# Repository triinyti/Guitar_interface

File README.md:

# Guitar_interface
Custom designed guitar interface for 48kHz/24 bit audio transmission via UAC (USB Audio Class) and mic output.

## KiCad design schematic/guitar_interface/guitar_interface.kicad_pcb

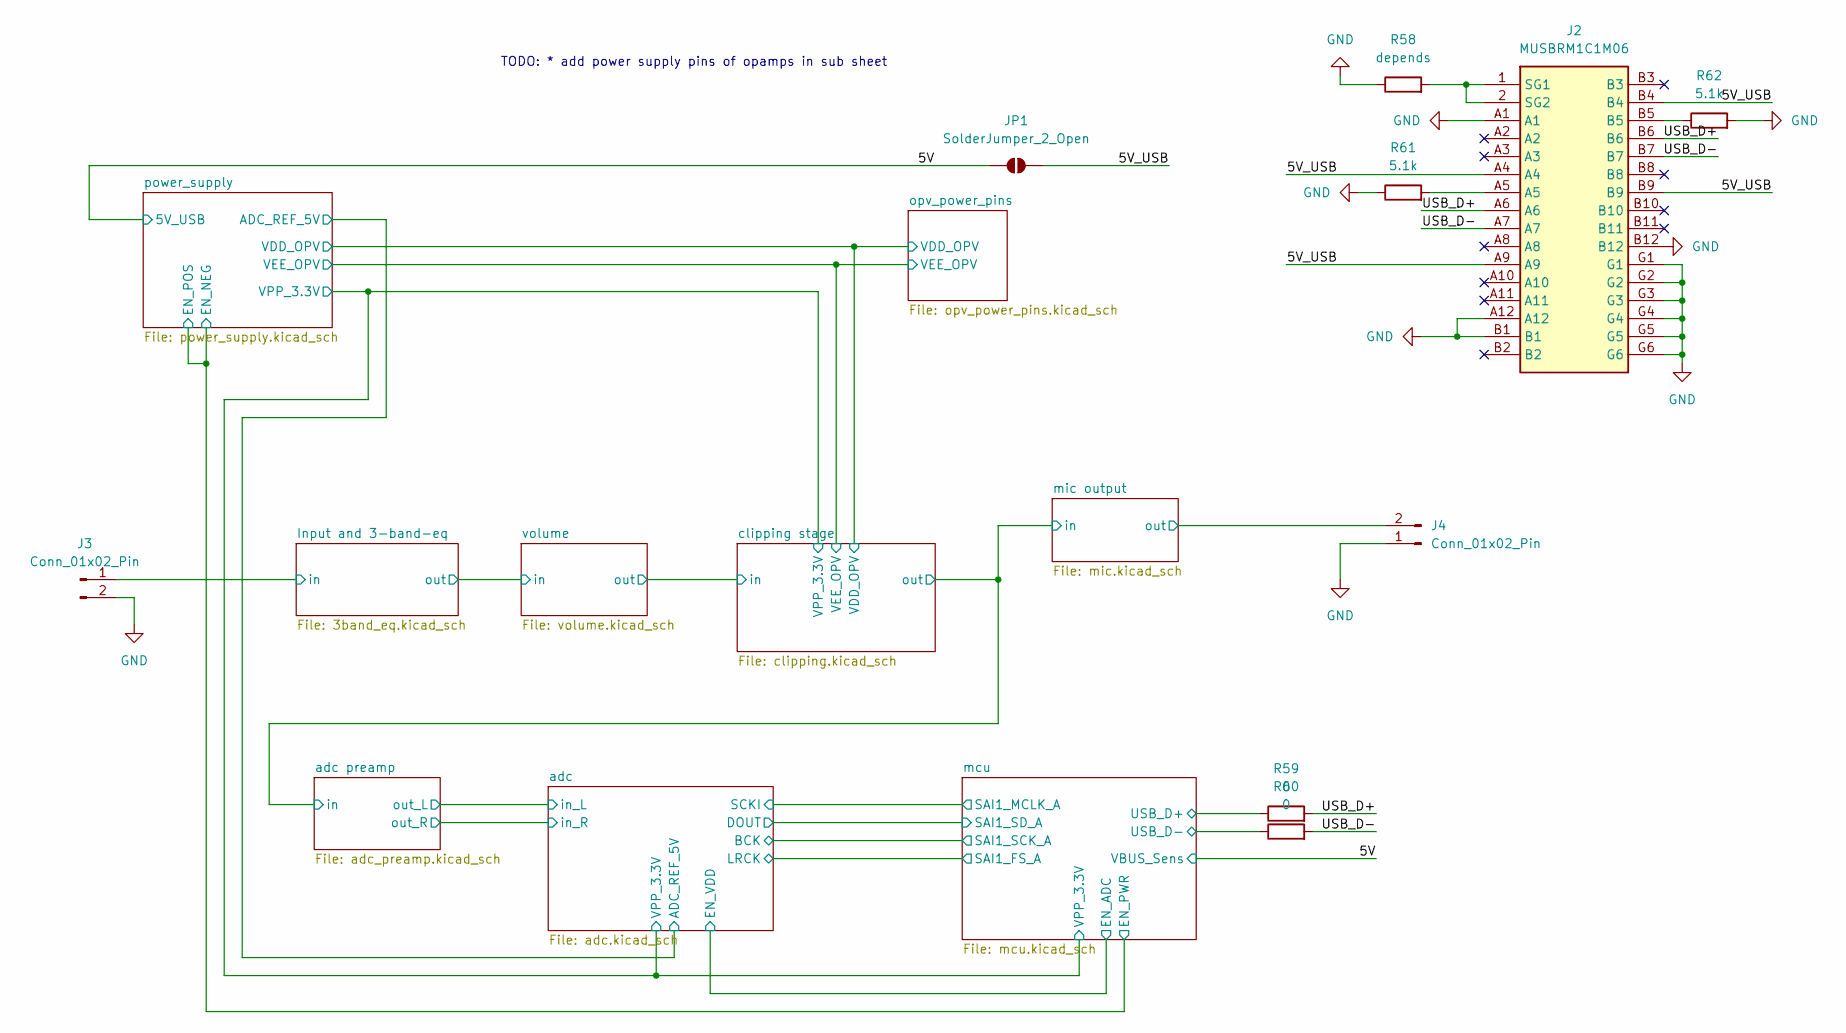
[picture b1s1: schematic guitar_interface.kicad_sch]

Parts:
J2: MUSBRM1C1M06; Mouser Part Number 523-MUSBRM1C1M06
J3, J4: Conn_01x02_Pin; PinSocket_1x02_P2.54mm_Vertical
JP1: SolderJumper_2_Open; SolderJumper-2_P1.3mm_Open_RoundedPad1.0x1.5mm
R58: depends; R_0603_1608Metric_Pad0.98x0.95mm_HandSolder
R59, R60: 0; R_0603_1608Metric_Pad0.98x0.95mm_HandSolder
R61, R62: 5.1k; R_0603_1608Metric_Pad0.98x0.95mm_HandSolder

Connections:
/5V: JP1.1 (A); also elsewhere on the board
/5V_USB: J2.A4, J2.A9, J2.B4, J2.B9, JP1.2 (B)
/Input and 3-band-eq/in: J3.1; also elsewhere on the board
/USB_D+: J2.A6, J2.B6, R59.2
/USB_D-: J2.A7, J2.B7, R60.2
/mcu/USB_D+: R59.1; also elsewhere on the board
/mcu/USB_D-: R60.1; also elsewhere on the board
/mic output/out: J4.2; also elsewhere on the board
GND: J2.A1, J2.A12, J2.B1, J2.B12, J2.G1, J2.G2, J2.G3, J2.G4, J2.G5, J2.G6, J3.2, J4.1, R58.1, R61.1, R62.2; also elsewhere on the board
unnamed: J2.A5, R61.2
unnamed: J2.B5, R62.1
unnamed: J2.1 (SG1), J2.2 (SG2), R58.2

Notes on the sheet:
TODO: * add power supply pins of opamps in sub sheet

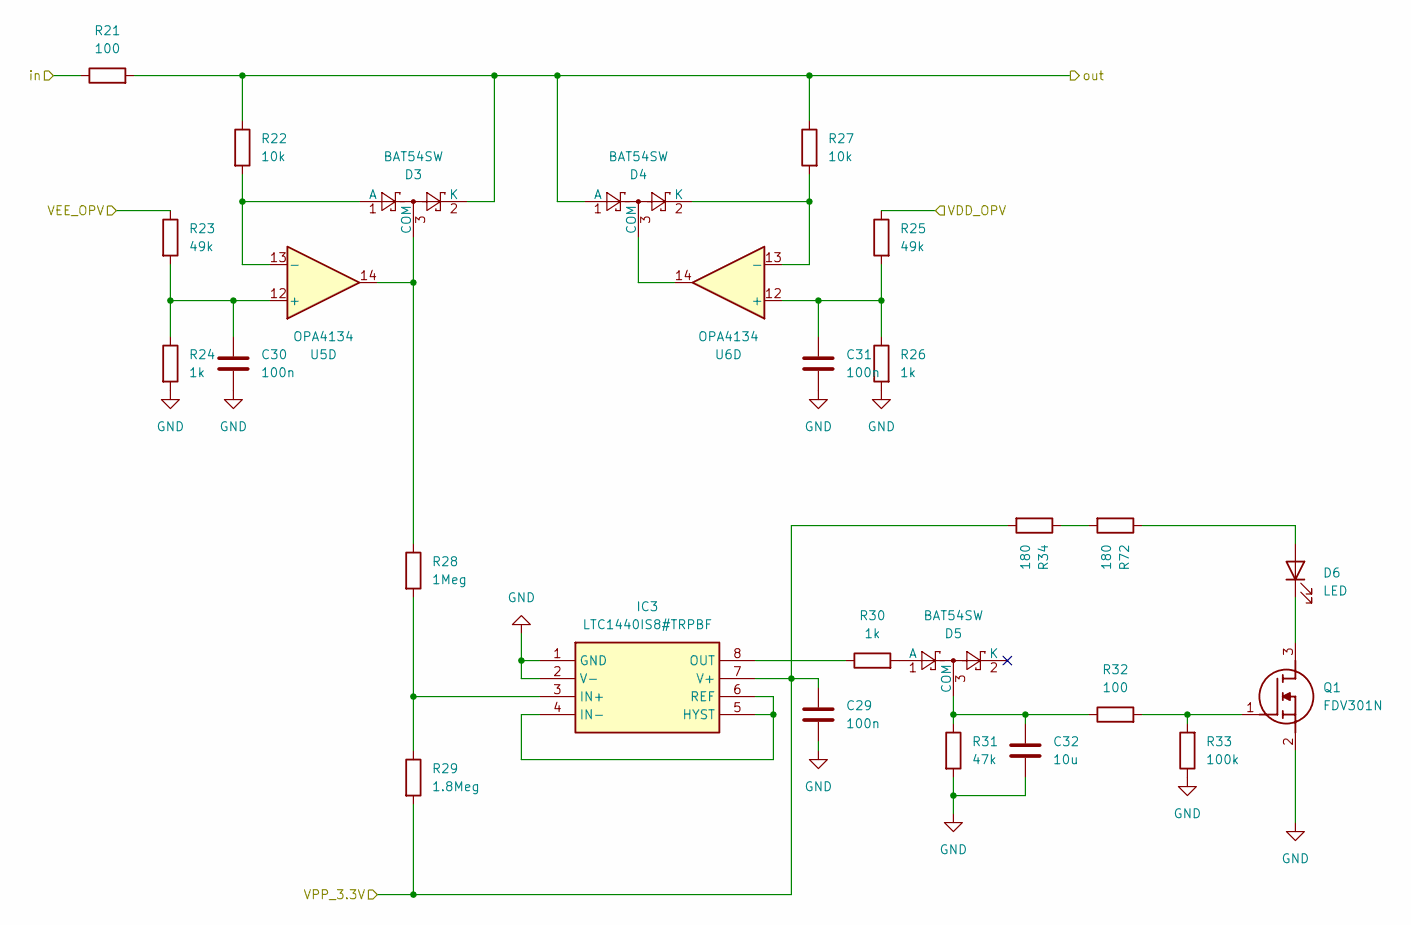
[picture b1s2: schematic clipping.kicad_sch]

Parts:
C29, C30, C31: 100n; C_0402_1005Metric_Pad0.74x0.62mm_HandSolder
C32: 10u; C_0603_1608Metric_Pad1.08x0.95mm_HandSolder
D3, D4, D5: BAT54SW; SOT-323_SC-70
D6: LED; LED_0603_1608Metric_Pad1.05x0.95mm_HandSolder
IC3: LTC1440IS8#TRPBF; SOIC127P599X175-8N; Mouser Part Number 584-LTC1440IS8#TRPBF
Q1: FDV301N; SOT96P237X111-3N; Mouser Part Number 512-FDV301N
R21, R32: 100; R_0603_1608Metric_Pad0.98x0.95mm_HandSolder
R22, R27: 10k; R_0603_1608Metric_Pad0.98x0.95mm_HandSolder
R23, R25: 49k; R_0603_1608Metric_Pad0.98x0.95mm_HandSolder
R24, R26, R30: 1k; R_0603_1608Metric_Pad0.98x0.95mm_HandSolder
R28: 1Meg; R_0603_1608Metric_Pad0.98x0.95mm_HandSolder
R29: 1.8Meg; R_0603_1608Metric_Pad0.98x0.95mm_HandSolder
R31: 47k; R_0603_1608Metric_Pad0.98x0.95mm_HandSolder
R33: 100k; R_0603_1608Metric_Pad0.98x0.95mm_HandSolder
R34, R72: 180; R_0603_1608Metric_Pad0.98x0.95mm_HandSolder
U5, U6: OPA4134; SOIC-14_3.9x8.7mm_P1.27mm

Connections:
/adc preamp/in: D3.2 (K), D4.1 (A), R21.2, R22.1, R27.1; also elsewhere on the board
/adc/VPP_3.3V: C29.1, IC3.7 (V+), R29.2, R34.2; also elsewhere on the board
/clipping stage/VDD_OPV: R25.1; also elsewhere on the board
/clipping stage/VEE_OPV: R23.1; also elsewhere on the board
/clipping stage/in: R21.1; also elsewhere on the board
GND: C29.2, C30.2, C31.2, C32.2, IC3.1 (GND), IC3.2 (V-), Q1.2 (S), R24.2, R26.2, R31.2, R33.1; also elsewhere on the board
unnamed: D3.1 (A), R22.2, U5.13 (-)
unnamed: D3.3 (COM), R28.1, U5.14
unnamed: D4.3 (COM), U6.14
unnamed: D4.2 (K), R27.2, U6.13 (-)
unnamed: D5.1 (A), R30.2
unnamed: C32.1, D5.3 (COM), R31.1, R32.1
unnamed: D6.2 (A), R72.1
unnamed: D6.1 (K), Q1.3 (D)
unnamed: IC3.4 (IN-), IC3.5 (HYST), IC3.6 (REF)
unnamed: IC3.3 (IN+), R28.2, R29.1
unnamed: IC3.8 (OUT), R30.1
unnamed: Q1.1 (G), R32.2, R33.2
unnamed: R34.1, R72.2
unnamed: C30.1, R23.2, R24.1, U5.12 (+)
unnamed: C31.1, R25.2, R26.1, U6.12 (+)

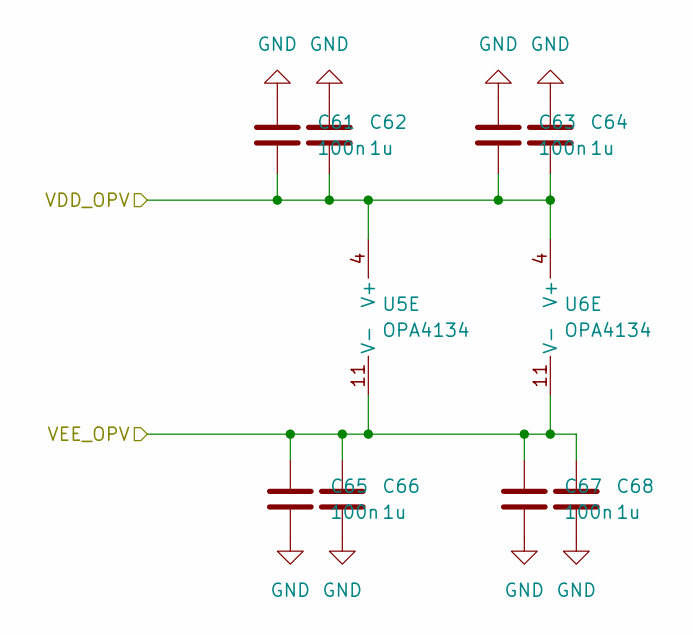
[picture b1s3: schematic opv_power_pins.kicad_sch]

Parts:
C61, C63, C65, C67: 100n; C_0402_1005Metric_Pad0.74x0.62mm_HandSolder
C62, C64, C66, C68: 1u; C_0603_1608Metric_Pad1.08x0.95mm_HandSolder
U5, U6: OPA4134; SOIC-14_3.9x8.7mm_P1.27mm

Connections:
/clipping stage/VDD_OPV: C61.2, C62.2, C63.2, C64.2, U5.4 (V+), U6.4 (V+); also elsewhere on the board
/clipping stage/VEE_OPV: C65.1, C66.1, C67.1, C68.1, U5.11 (V-), U6.11 (V-); also elsewhere on the board
GND: C61.1, C62.1, C63.1, C64.1, C65.2, C66.2, C67.2, C68.2; also elsewhere on the board

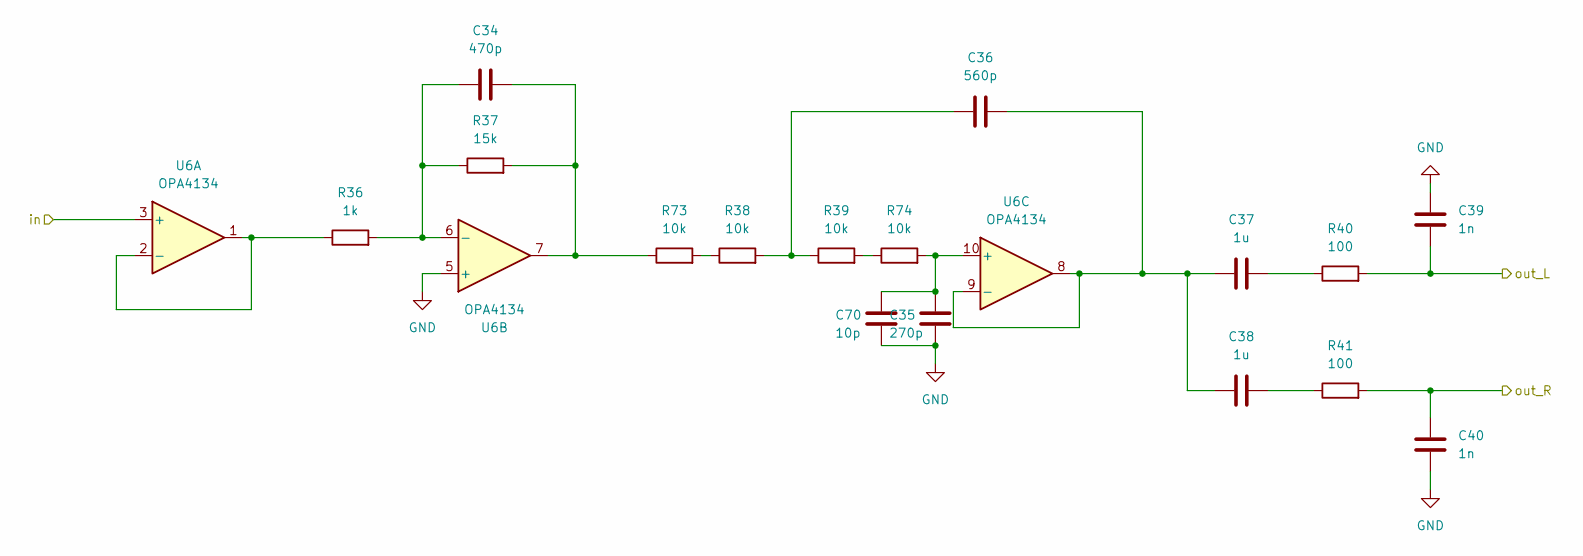
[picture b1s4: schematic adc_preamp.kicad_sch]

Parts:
C34: 470p; C_0603_1608Metric_Pad1.08x0.95mm_HandSolder
C35: 270p; C_0402_1005Metric_Pad0.74x0.62mm_HandSolder
C36: 560p; C_0805_2012Metric_Pad1.18x1.45mm_HandSolder
C37, C38: 1u; C_0603_1608Metric_Pad1.08x0.95mm_HandSolder
C39, C40: 1n; C_0402_1005Metric_Pad0.74x0.62mm_HandSolder
C70: 10p; C_0603_1608Metric_Pad1.08x0.95mm_HandSolder
R36: 1k; R_0603_1608Metric_Pad0.98x0.95mm_HandSolder
R37: 15k; R_0603_1608Metric_Pad0.98x0.95mm_HandSolder
R38, R39, R73, R74: 10k; R_0603_1608Metric_Pad0.98x0.95mm_HandSolder
R40, R41: 100; R_0603_1608Metric_Pad0.98x0.95mm_HandSolder
U6: OPA4134; SOIC-14_3.9x8.7mm_P1.27mm

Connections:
/adc preamp/in: U6.3 (+); also elsewhere on the board
/adc preamp/out_L: C39.1, R40.2; also elsewhere on the board
/adc preamp/out_R: C40.2, R41.2; also elsewhere on the board
GND: C35.2, C39.2, C40.1, C70.2, U6.5 (+); also elsewhere on the board
unnamed: C34.2, R37.2, R73.1, U6.7
unnamed: C36.1, R38.2, R39.1
unnamed: C37.2, R40.1
unnamed: C38.2, R41.1
unnamed: R38.1, R73.2
unnamed: R39.2, R74.1
unnamed: R36.1, U6.1, U6.2 (-)
unnamed: C34.1, R36.2, R37.1, U6.6 (-)
unnamed: C35.1, C70.1, R74.2, U6.10 (+)
unnamed: C36.2, C37.1, C38.1, U6.8, U6.9 (-)

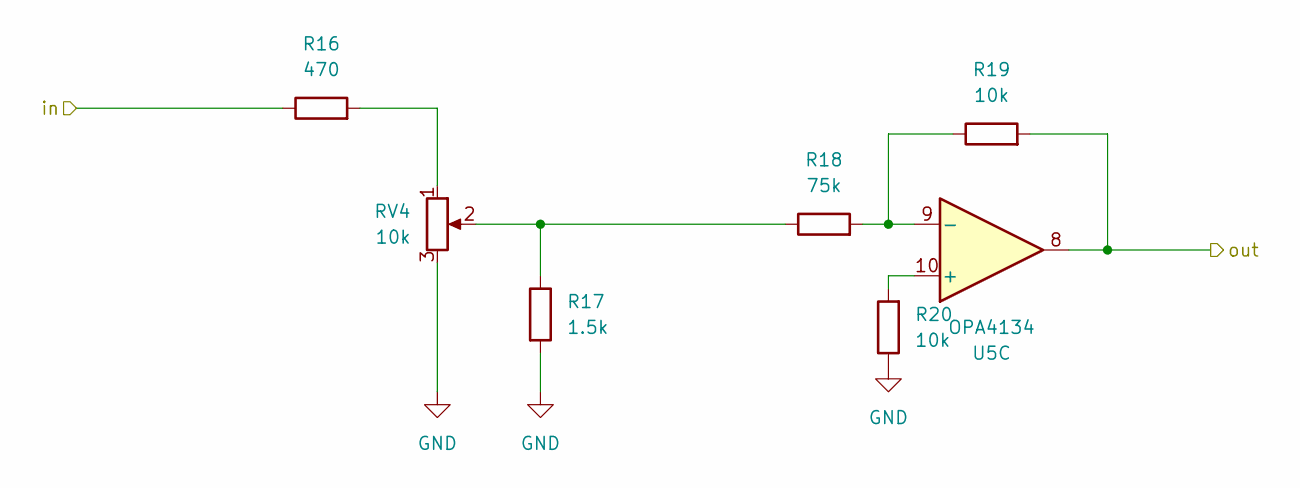
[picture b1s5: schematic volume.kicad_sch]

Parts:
R16: 470; R_0603_1608Metric_Pad0.98x0.95mm_HandSolder
R17: 1.5k; R_0603_1608Metric_Pad0.98x0.95mm_HandSolder
R18: 75k; R_0603_1608Metric_Pad0.98x0.95mm_HandSolder
R19, R20: 10k; R_0603_1608Metric_Pad0.98x0.95mm_HandSolder
RV4: 10k; PinHeader_1x03_P2.54mm_Vertical
U5: OPA4134; SOIC-14_3.9x8.7mm_P1.27mm

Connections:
/Input and 3-band-eq/out: R16.1; also elsewhere on the board
/clipping stage/in: R19.2, U5.8; also elsewhere on the board
GND: R17.2, R20.1, RV4.3; also elsewhere on the board
unnamed: R16.2, RV4.1
unnamed: R17.1, R18.1, RV4.2
unnamed: R20.2, U5.10 (+)
unnamed: R18.2, R19.1, U5.9 (-)

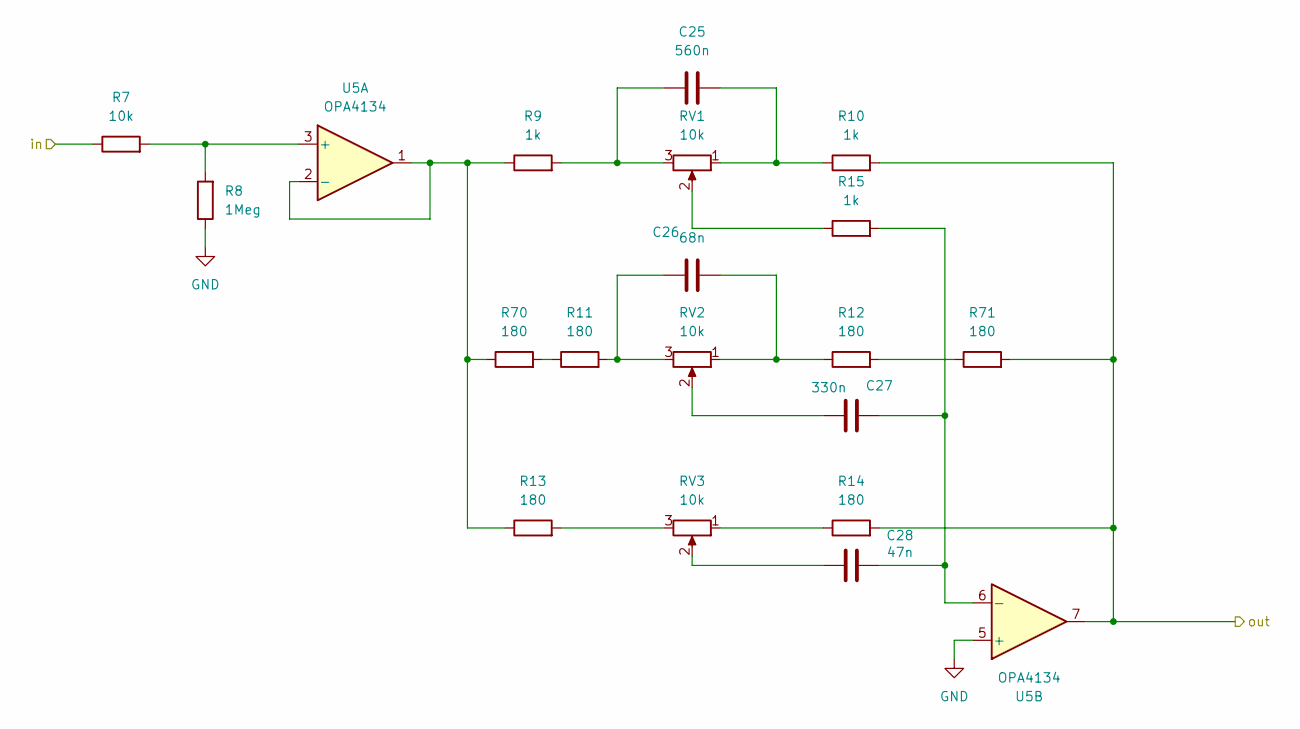
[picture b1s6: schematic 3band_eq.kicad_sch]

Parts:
C25: 560n; C_0805_2012Metric_Pad1.18x1.45mm_HandSolder
C26: 68n; C_0805_2012Metric_Pad1.18x1.45mm_HandSolder
C27: 330n; C_0805_2012Metric_Pad1.18x1.45mm_HandSolder
C28: 47n; C_0603_1608Metric_Pad1.08x0.95mm_HandSolder
R7: 10k; R_0603_1608Metric_Pad0.98x0.95mm_HandSolder
R8: 1Meg; R_0603_1608Metric_Pad0.98x0.95mm_HandSolder
R9, R10, R15: 1k; R_0603_1608Metric_Pad0.98x0.95mm_HandSolder
R11, R12, R13, R14, R70, R71: 180; R_0603_1608Metric_Pad0.98x0.95mm_HandSolder
RV1, RV2, RV3: 10k; PinHeader_1x03_P2.54mm_Vertical
U5: OPA4134; SOIC-14_3.9x8.7mm_P1.27mm

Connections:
/Input and 3-band-eq/in: R7.1; also elsewhere on the board
/Input and 3-band-eq/out: R10.2, R14.2, R71.2, U5.7; also elsewhere on the board
GND: R8.1, U5.5 (+); also elsewhere on the board
unnamed: C25.1, R9.2, RV1.3
unnamed: C25.2, R10.1, RV1.1
unnamed: C26.1, R11.2, RV2.3
unnamed: C26.2, R12.1, RV2.1
unnamed: C27.1, RV2.2
unnamed: C28.1, RV3.2
unnamed: R11.1, R70.2
unnamed: R12.2, R71.1
unnamed: R13.2, RV3.3
unnamed: R14.1, RV3.1
unnamed: R15.1, RV1.2
unnamed: R7.2, R8.2, U5.3 (+)
unnamed: R9.1, R13.1, R70.1, U5.1, U5.2 (-)
unnamed: C27.2, C28.2, R15.2, U5.6 (-)

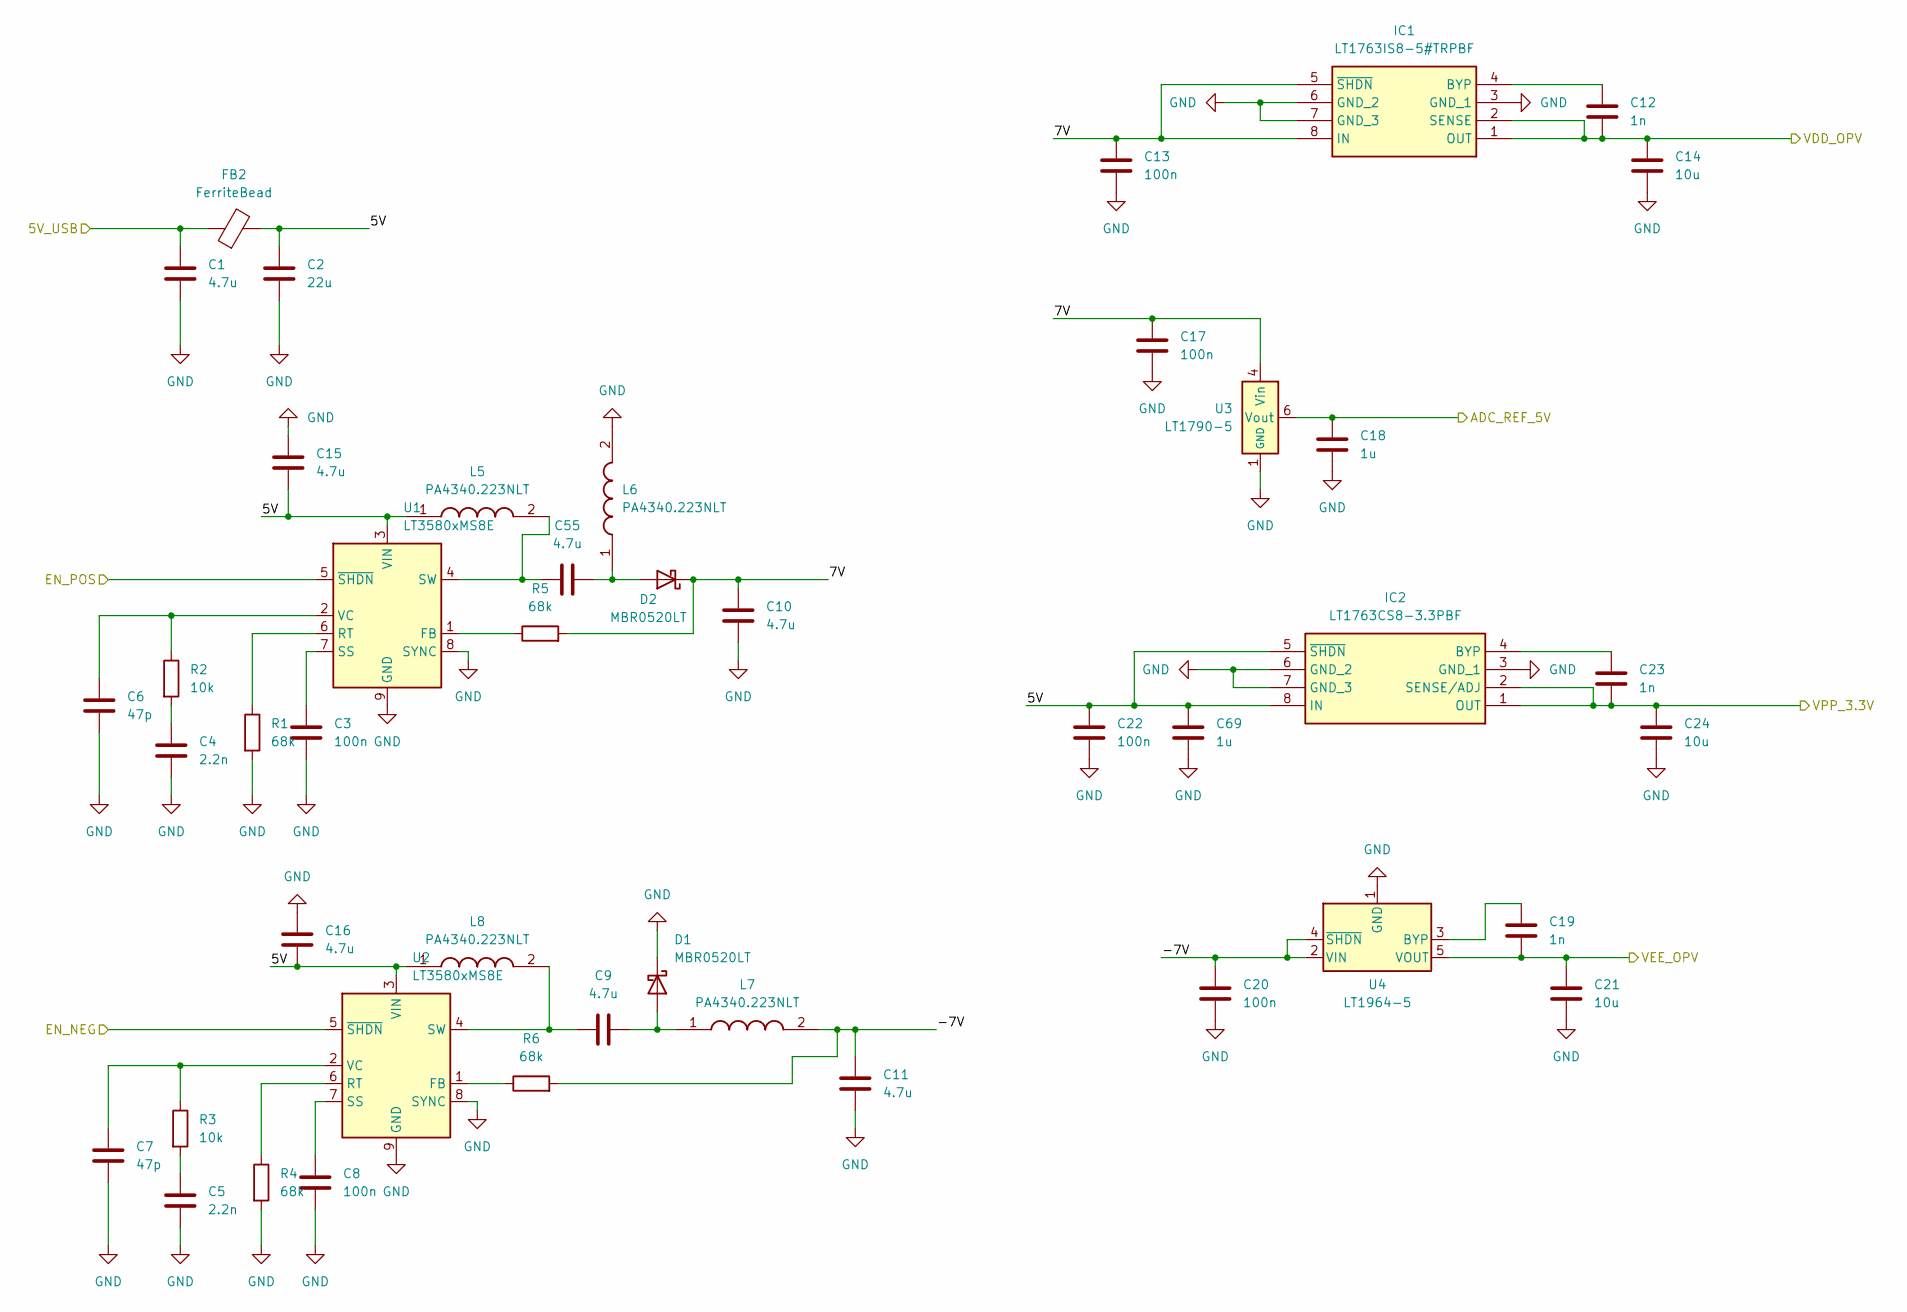
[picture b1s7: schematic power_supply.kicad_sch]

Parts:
C1, C9, C10, C11, C15, C16, C55: 4.7u; C_0805_2012Metric_Pad1.18x1.45mm_HandSolder
C2: 22u; C_0603_1608Metric_Pad1.08x0.95mm_HandSolder
C3, C8, C13, C17, C20, C22: 100n; C_0402_1005Metric_Pad0.74x0.62mm_HandSolder
C4, C5: 2.2n; C_0402_1005Metric_Pad0.74x0.62mm_HandSolder
C6, C7: 47p; C_0402_1005Metric_Pad0.74x0.62mm_HandSolder
C12, C19, C23: 1n; C_0402_1005Metric_Pad0.74x0.62mm_HandSolder
C14, C21, C24: 10u; C_0603_1608Metric_Pad1.08x0.95mm_HandSolder
C18, C69: 1u; C_0603_1608Metric_Pad1.08x0.95mm_HandSolder
D1, D2: MBR0520LT; D_SOD-123
FB2: FerriteBead; R_1206_3216Metric
IC1: LT1763IS8-5#TRPBF; SOIC127P599X175-8N; Mouser Part Number 584-LT1763IS8-5TRPBF
IC2: LT1763CS8-3.3PBF; SOIC127P599X175-8N; Manufacturer_Part_Number LT1763CS8-3.3PBF
L5, L6, L7, L8: PA4340.223NLT; INDPM6054X300N; Mouser Part Number 673-PA4340.223NLT
R1, R4, R5, R6: 68k; R_0603_1608Metric_Pad0.98x0.95mm_HandSolder
R2, R3: 10k; R_0603_1608Metric_Pad0.98x0.95mm_HandSolder
U1, U2: LT3580xMS8E; MSOP-8-1EP_3x3mm_P0.65mm_EP1.68x1.88mm
U3: LT1790-5; TSOT-23-6
U4: LT1964-5; TSOT-23-5

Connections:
/5V: C1.1, FB2.1; also elsewhere on the board
/adc/ADC_REF_5V: C18.1, U3.6 (Vout); also elsewhere on the board
/adc/VPP_3.3V: C23.2, C24.1, IC2.1 (OUT), IC2.2 (SENSE/ADJ); also elsewhere on the board
/clipping stage/VDD_OPV: C12.2, C14.1, IC1.1 (OUT), IC1.2 (SENSE); also elsewhere on the board
/clipping stage/VEE_OPV: C19.2, C21.1, U4.5 (VOUT); also elsewhere on the board
/mcu/EN_PWR: U1.5 (~SHDN), U2.5 (~SHDN); also elsewhere on the board
/power_supply/5V: C2.1, C15.1, C16.1, C22.1, C69.1, FB2.2, IC2.5 (~SHDN), IC2.8 (IN), L5.1, L8.1, U1.3 (VIN), U2.3 (VIN)
/power_supply/7V: C10.2, C13.1, C17.1, D2.1 (K), IC1.5 (~SHDN), IC1.8 (IN), R5.2, U3.4 (Vin)
/power_supply/-7V: C11.2, C20.1, L7.2, R6.2, U4.2 (VIN), U4.4 (~SHDN)
GND: C1.2, C2.2, C3.2, C4.2, C5.2, C6.2, C7.2, C8.2, C10.1, C11.1, C13.2, C14.2, C15.2, C16.2, C17.2, C18.2, C20.2, C21.2, C22.2, C24.2, C69.2, D1.1 (K), IC1.3 (GND_1), IC1.6 (GND_2), IC1.7 (GND_3), IC2.3 (GND_1), IC2.6 (GND_2), IC2.7 (GND_3), L6.2, R1.2, R4.2, U1.8 (SYNC), U1.9 (GND), U2.8 (SYNC), U2.9 (GND), U3.1 (GND), U3.2 (GND), U4.1 (GND); also elsewhere on the board
unnamed: C4.1, R2.2
unnamed: C5.1, R3.2
unnamed: C9.2, D1.2 (A), L7.1
unnamed: C55.1, D2.2 (A), L6.1
unnamed: C12.1, IC1.4 (BYP)
unnamed: C23.1, IC2.4 (BYP)
unnamed: R5.1, U1.1 (FB)
unnamed: R1.1, U1.6 (RT)
unnamed: C3.1, U1.7 (SS)
unnamed: C55.2, L5.2, U1.4 (SW)
unnamed: C6.1, R2.1, U1.2 (VC)
unnamed: R6.1, U2.1 (FB)
unnamed: R4.1, U2.6 (RT)
unnamed: C8.1, U2.7 (SS)
unnamed: C9.1, L8.2, U2.4 (SW)
unnamed: C7.1, R3.1, U2.2 (VC)
unnamed: C19.1, U4.3 (BYP)

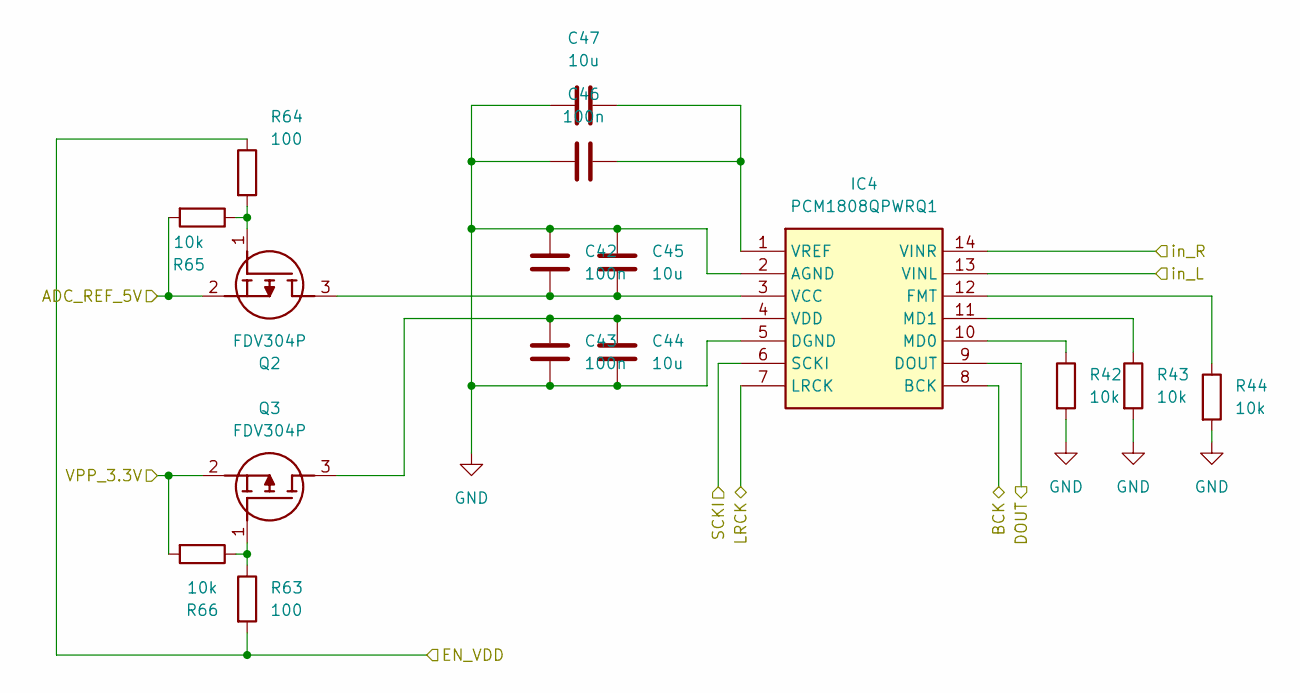
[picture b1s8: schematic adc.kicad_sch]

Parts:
C42, C43, C46: 100n; C_0402_1005Metric_Pad0.74x0.62mm_HandSolder
C44, C45, C47: 10u; C_0603_1608Metric_Pad1.08x0.95mm_HandSolder
IC4: PCM1808QPWRQ1; SOP65P640X120-14N; Mouser Part Number 595-PCM1808QPWRQ1
Q2, Q3: FDV304P; SOT95P251X112-3N; Mouser Part Number 512-FDV304P
R42, R43, R44, R65, R66: 10k; R_0603_1608Metric_Pad0.98x0.95mm_HandSolder
R63, R64: 100; R_0603_1608Metric_Pad0.98x0.95mm_HandSolder

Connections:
/adc preamp/out_L: IC4.13 (VINL); also elsewhere on the board
/adc preamp/out_R: IC4.14 (VINR); also elsewhere on the board
/adc/ADC_REF_5V: Q2.2 (S), R65.2; also elsewhere on the board
/adc/BCK: IC4.8 (BCK); also elsewhere on the board
/adc/DOUT: IC4.9 (DOUT); also elsewhere on the board
/adc/EN_VDD: R63.2, R64.1; also elsewhere on the board
/adc/LRCK: IC4.7 (LRCK); also elsewhere on the board
/adc/SCKI: IC4.6 (SCKI); also elsewhere on the board
/adc/VPP_3.3V: Q3.2 (S), R66.2; also elsewhere on the board
GND: C42.2, C43.1, C44.1, C45.2, C46.2, C47.2, IC4.2 (AGND), IC4.5 (DGND), R42.2, R43.2, R44.2; also elsewhere on the board
unnamed: IC4.12 (FMT), R44.1
unnamed: IC4.10 (MD0), R42.1
unnamed: IC4.11 (MD1), R43.1
unnamed: C42.1, C45.1, IC4.3 (VCC), Q2.3 (D)
unnamed: C43.2, C44.2, IC4.4 (VDD), Q3.3 (D)
unnamed: C46.1, C47.1, IC4.1 (VREF)
unnamed: Q2.1 (G), R64.2, R65.1
unnamed: Q3.1 (G), R63.1, R66.1

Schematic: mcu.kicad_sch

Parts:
C41, C48, C49, C50, C51, C52, C59, C60: 100n; C_0402_1005Metric_Pad0.74x0.62mm_HandSolder
C53, C56: 15p; C_0201_0603Metric_Pad0.64x0.40mm_HandSolder
C54: 4.7u; C_0805_2012Metric_Pad1.18x1.45mm_HandSolder
C57, C58: 2.2u; C_0603_1608Metric_Pad1.08x0.95mm_HandSolder
D7, D8: ESD321DPYR; DPY_R-PX1SON-N2_; Mouser Part Number 595-ESD321DPYR
D9: LED; LED_0603_1608Metric_Pad1.05x0.95mm_HandSolder
J1: Conn_ST_STDC14; FTSH-107-XX-YYY-D-K
R45, R47, R48, R49, R50, R53, R54, R55, R56, R57, R67: 470; R_0603_1608Metric_Pad0.98x0.95mm_HandSolder
R46, R51, R52: 10k; R_0603_1608Metric_Pad0.98x0.95mm_HandSolder
R68, R69: 0; R_0603_1608Metric_Pad0.98x0.95mm_HandSolder
U8: STM32F446VETx; LQFP-100_14x14mm_P0.5mm
Y1: LFXTAL032878; Manufacturer_Part_Number LFXTAL032878

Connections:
/5V: R51.2; also elsewhere on the board
/adc/BCK: R48.2; also elsewhere on the board
/adc/DOUT: R49.2; also elsewhere on the board
/adc/EN_VDD: R69.2; also elsewhere on the board
/adc/LRCK: R47.2; also elsewhere on the board
/adc/SCKI: R50.1; also elsewhere on the board
/adc/VPP_3.3V: C41.1, C48.1, C49.1, C50.1, C51.1, C52.1, C54.1, C59.1, C60.1, J1.3 (VCC), R46.2, U8.6 (VBAT), U8.11 (VDD), U8.19 (VDD), U8.21 (VREF+), U8.22 (VDDA), U8.28 (VDD), U8.50 (VDD), U8.75 (VDD), U8.100 (VDD); also elsewhere on the board
/mcu/EN_PWR: R68.2; also elsewhere on the board
/mcu/JCLK: R53.2, U8.76 (PA14)
/mcu/JRCLK: R57.2, U8.90 (PB4)
/mcu/JTDI: R56.2, U8.77 (PA15)
/mcu/JTDO: R55.2, U8.89 (PB3)
/mcu/JTMS: R54.2, U8.72 (PA13)
/mcu/USB_D+: D8.1, U8.71 (PA12); also elsewhere on the board
/mcu/USB_D-: D7.1, U8.70 (PA11); also elsewhere on the board
GND: C41.2, C48.2, C49.2, C50.2, C51.2, C52.2, C53.1, C54.2, C56.1, C57.2, C58.2, C59.2, C60.2, D7.2, D8.2, D9.1 (K), J1.5 (GND), J1.7 (GND), R45.2, R52.2, U8.10 (VSS), U8.20 (VSSA), U8.27 (VSS), U8.49 (VSS), U8.74 (VSS), U8.99 (VSS), Y1.1 (CRYSTAL_1), Y1.2 (GND&LID_1); also elsewhere on the board
unnamed: D9.2 (A), R67.1
unnamed: J1.11 (GNDDetect), R45.1
unnamed: J1.6 (JCLK/SWCLK), R53.1
unnamed: J1.9 (JRCLK/NC), R57.1
unnamed: J1.10 (JTDI/NC), R56.1
unnamed: J1.8 (JTDO/SWO), R55.1
unnamed: J1.4 (JTMS/SWDIO), R54.1
unnamed: J1.12 (~RST), R46.1, U8.14 (NRST)
unnamed: R52.1, U8.94 (BOOT0)
unnamed: R67.2, U8.30 (PA5)
unnamed: R51.1, U8.68 (PA9)
unnamed: R68.1, U8.35 (PB0)
unnamed: R69.1, U8.36 (PB1)
unnamed: R50.2, U8.1 (PE2)
unnamed: R47.1, U8.3 (PE4)
unnamed: R48.1, U8.4 (PE5)
unnamed: R49.1, U8.5 (PE6)
unnamed: C53.2, U8.12 (PH0), Y1.3 (CRYSTAL_2)
unnamed: C56.2, U8.13 (PH1), Y1.4 (GND&LID_2)
unnamed: C57.1, U8.48 (VCAP_1)
unnamed: C58.1, U8.73 (VCAP_2)

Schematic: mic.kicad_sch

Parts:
C33: 470u; CAPAE660X980N
R35: 2.2k; R_0603_1608Metric_Pad0.98x0.95mm_HandSolder

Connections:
/adc preamp/in: C33.2; also elsewhere on the board
/mic output/out: C33.1, R35.1; also elsewhere on the board
GND: R35.2; also elsewhere on the board

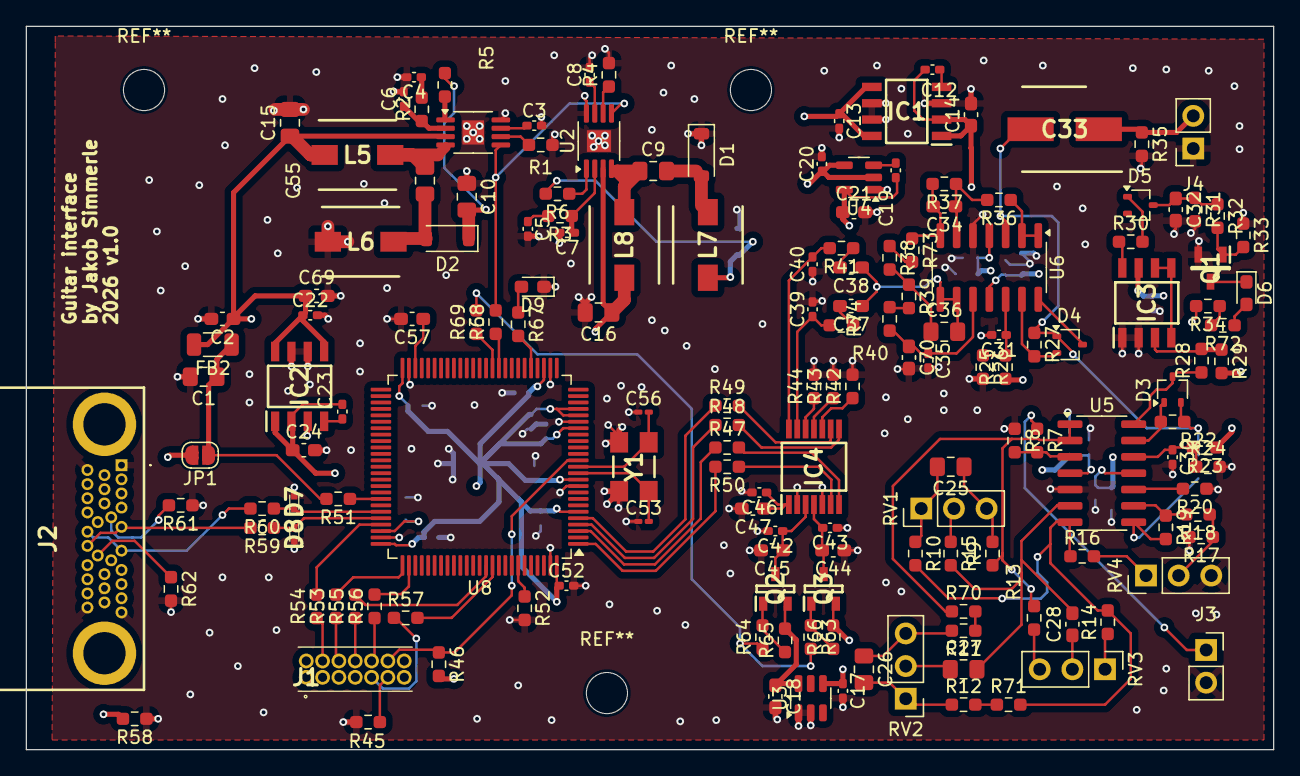
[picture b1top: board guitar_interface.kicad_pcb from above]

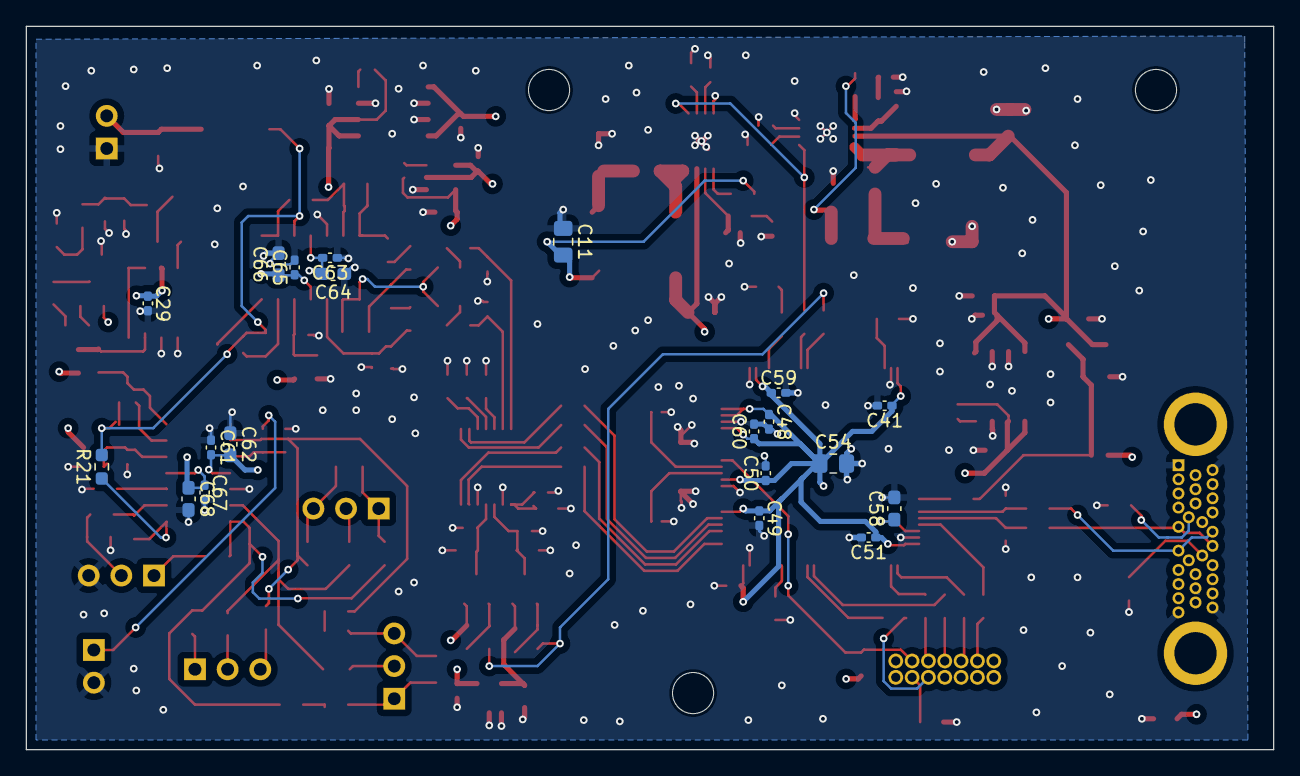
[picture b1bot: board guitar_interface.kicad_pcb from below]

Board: 4 copper layers, 97.0 x 56.2 mm, 182 parts (20 on the bottom side), 124 nets.

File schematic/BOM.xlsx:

Done | Reference | Value | Footprint | Datasheet | Qty | DNP | Exclude from BOM | Exclude from Board
x | C1,C9,C10,C11,C15,C16,C54,C55 | 4.7u |  | ~ | 8
x | C2 | 22u
x | L1,L2,L3,L4 | 22u |  | ~ | 5
x | C3,C8,C13,C17,C20,C22,C30,C31,C41,C42,C43,C46,C48,C49,C50,C51,C52,C59,C60,C61,C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 | 100n | Capacitor_SMD:C_0603_1608Metric_Pad1.08x0.95mm_HandSolder | ~ | 23
x | C4,C5 | 2.2n | Capacitor_SMD:C_0603_1608Metric_Pad1.08x0.95mm_HandSolder | ~ | 2
x | C6,C7 | 47p |  | ~ | 2
x | C12,C23,C39,C40,C19 | 1n | Capacitor_SMD:C_0603_1608Metric_Pad1.08x0.95mm_HandSolder | ~ | 4
x | C14,C21,C24,C32,C44,C45,C47 | 10u |  | ~ | 7
x | C18,C37,C38,C62,C64,C66,C68,C69 | 1u |  | ~ | 8
x | C25 | 560n | Capacitor_SMD:C_0603_1608Metric_Pad1.08x0.95mm_HandSolder | ~ | 1
x | C26 | 68n | Capacitor_SMD:C_0603_1608Metric_Pad1.08x0.95mm_HandSolder | ~ | 1
x | C27 | 330n | Capacitor_SMD:C_0603_1608Metric_Pad1.08x0.95mm_HandSolder | ~ | 1
x | C28 | 47n | Capacitor_SMD:C_0603_1608Metric_Pad1.08x0.95mm_HandSolder | ~ | 1
x | C33 | 470u |  | ~ | 1
x | C34 | 470p |  | ~ | 1
x | C35 | 280p |  | ~ | 1
x | C36 | 560p |  | ~ | 1
x | C53,C56 | 15p |  | ~ | 2
x | C57,C58 | 2.2u |  | ~ | 2
x | D1,D2 | MBR0520LT | Diode_SMD:D_SOD-123 | http://www.onsemi.com/pub_link/Collateral/MBR0520LT1-D.PDF | 2
x | D3,D4,D5 | BAT54SW | Package_TO_SOT_SMD:SOT-323_SC-70 | https://assets.nexperia.com/documents/data-sheet/BAT54W_SER.pdf | 3
x | D6,D9 | LED |  | ~ | 2
x | D7,D8 | ESD321DPYR |  | http://www.ti.com/lit/gpn/esd321 | 2
x | FB2 | FerriteBead |  | ~ | 1
x | IC1 | LT1763IS8-5#TRPBF |  | https://www.analog.com/media/en/technical-documentation/data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 | 1
x | IC2 | LT1763CS8-3.3PBF |  | https://www.analog.com/media/en/technical-documentation/data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 | 1
x | IC3 | LTC1440IS8#TRPBF |  | https://www.analog.com/media/en/technical-documentation/data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 | 1
x | IC4 | PCM1808QPWRQ1 |  | http://www.ti.com/lit/ds/symlink/pcm1808-q1.pdf | 1
x | J1 | Conn_ST_STDC14 |  | https://www.st.com/content/ccc/resource/technical/document/u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 | 1
x | J2 | MUSBRM1C1M06 | SamacSys_Parts:MUSBRM1C1M06 | https://cdn.amphenol-cs.com/media/wysiwyg/files/drawing/musb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 | 1
x | J3,J4 | Conn_01x02_Pin | Connector_PinSocket_1.00mm:PinSocket_1x02_P1.00mm_Vertical | ~ | 2
x | JP1 | SolderJumper_2_Open | Jumper:SolderJumper-3_P1.3mm_Bridged123_Pad1.0x1.5mm | ~ | 1 |  | Von Bauteilliste ausgeschlossen
x | Q1 | FDV301N |  | https://www.onsemi.com/pub/Collateral/FDV301N-D.PDF | 1
x | Q2,Q3 | FDV304P | SamacSys_Parts:SOT95P251X112-3N | https://www.onsemi.com/pub/Collateral/FDV304P-D.PDF | 2
 | R1,R4,R5,R6 | 68k | Resistor_SMD:R_0603_1608Metric_Pad0.98x0.95mm_HandSolder | ~ | 4
 | R2,R3,R7,R19,R20,R22,R27,R38,R39,R42,R43,R44,R46,R51,R52,R65,R66,R73,R74 | 10k | Resistor_SMD:R_0603_1608Metric_Pad0.98x0.95mm_HandSolder | ~ | 19
 | R8,R28 | 1Meg | Resistor_SMD:R_0603_1608Metric_Pad0.98x0.95mm_HandSolder | ~ | 2
 | R9,R10,R15,R24,R26,R30,R36 | 1k | Resistor_SMD:R_0603_1608Metric_Pad0.98x0.95mm_HandSolder | ~ | 7
 | R11,R12,R13,R14,R34,R70,R71,R72 | 180 | Resistor_SMD:R_0603_1608Metric_Pad0.98x0.95mm_HandSolder | ~ | 8
 | R16,R45,R47,R48,R49,R50,R53,R54,R55,R56,R57,R67 | 470 | Resistor_SMD:R_0603_1608Metric_Pad0.98x0.95mm_HandSolder | ~ | 12
 | R17 | 1.5k | Resistor_SMD:R_0603_1608Metric_Pad0.98x0.95mm_HandSolder | ~ | 1
 | R18 | 75k | Resistor_SMD:R_0603_1608Metric_Pad0.98x0.95mm_HandSolder | ~ | 1
 | R21,R32,R40,R41,R63,R64 | 100 | Resistor_SMD:R_0603_1608Metric_Pad0.98x0.95mm_HandSolder | ~ | 6
 | R23,R25 | 49k | Resistor_SMD:R_0603_1608Metric_Pad0.98x0.95mm_HandSolder | ~ | 2
 | R29 | 1.8Meg | Resistor_SMD:R_0603_1608Metric_Pad0.98x0.95mm_HandSolder | ~ | 1
 | R31 | 47k | Resistor_SMD:R_0603_1608Metric_Pad0.98x0.95mm_HandSolder | ~ | 1
 | R33 | 100k | Resistor_SMD:R_0603_1608Metric_Pad0.98x0.95mm_HandSolder | ~ | 1
 | R35 | 2.2k | Resistor_SMD:R_0603_1608Metric_Pad0.98x0.95mm_HandSolder | ~ | 1
 | R37 | 15k | Resistor_SMD:R_0603_1608Metric_Pad0.98x0.95mm_HandSolder | ~ | 1
 | R58 | depends | Resistor_SMD:R_0603_1608Metric_Pad0.98x0.95mm_HandSolder | ~ | 1
 | R59,R60,R68,R69 | 0 | Resistor_SMD:R_0603_1608Metric_Pad0.98x0.95mm_HandSolder | ~ | 4
x | R61,R62 | 5.1k | Resistor_SMD:R_0603_1608Metric_Pad0.98x0.95mm_HandSolder | ~ | 2
x | RV1 | 10k |  | ~ | 1
x | RV2,RV3,RV4 | 10k |  | ~ | 3
x | U1,U2 | LT3580xMS8E | Package_SO:MSOP-8-1EP_3x3mm_P0.65mm_EP1.68x1.88mm | https://www.analog.com/media/en/technical-documentation/data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 | 2
x | U3 | LT1790-5 | Package_TO_SOT_SMD:TSOT-23-6 | https://www.analog.com/media/en/technical-documentation/data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 | 1
x | U4 | LT1964-5 | Package_TO_SOT_SMD:TSOT-23-5 | https://www.analog.com/media/en/technical-documentation/data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 | 1
x | U5,U6 | OPA4134 | Package_SO:SOIC-14_3.9x8.7mm_P1.27mm | http://www.ti.com/lit/ds/symlink/opa134.pdf | 2
x | U8 | STM32F446VETx | Package_QFP:LQFP-100_14x14mm_P0.5mm | https://www.st.com/resource/en/datasheet/stm32f446ve.pdf | 1
x | Y1 | Crystal_GND23 |  | ~ | 1

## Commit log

2026-02-11 add local files to system
2026-02-11 first scetch of audio pipeline and power supply layout
2026-02-12 fix minor issues and do most of the pcb layout
2026-02-12 refine layout fix, fix some minor issues, add additional ground planes on all layers, and add mounting holes
